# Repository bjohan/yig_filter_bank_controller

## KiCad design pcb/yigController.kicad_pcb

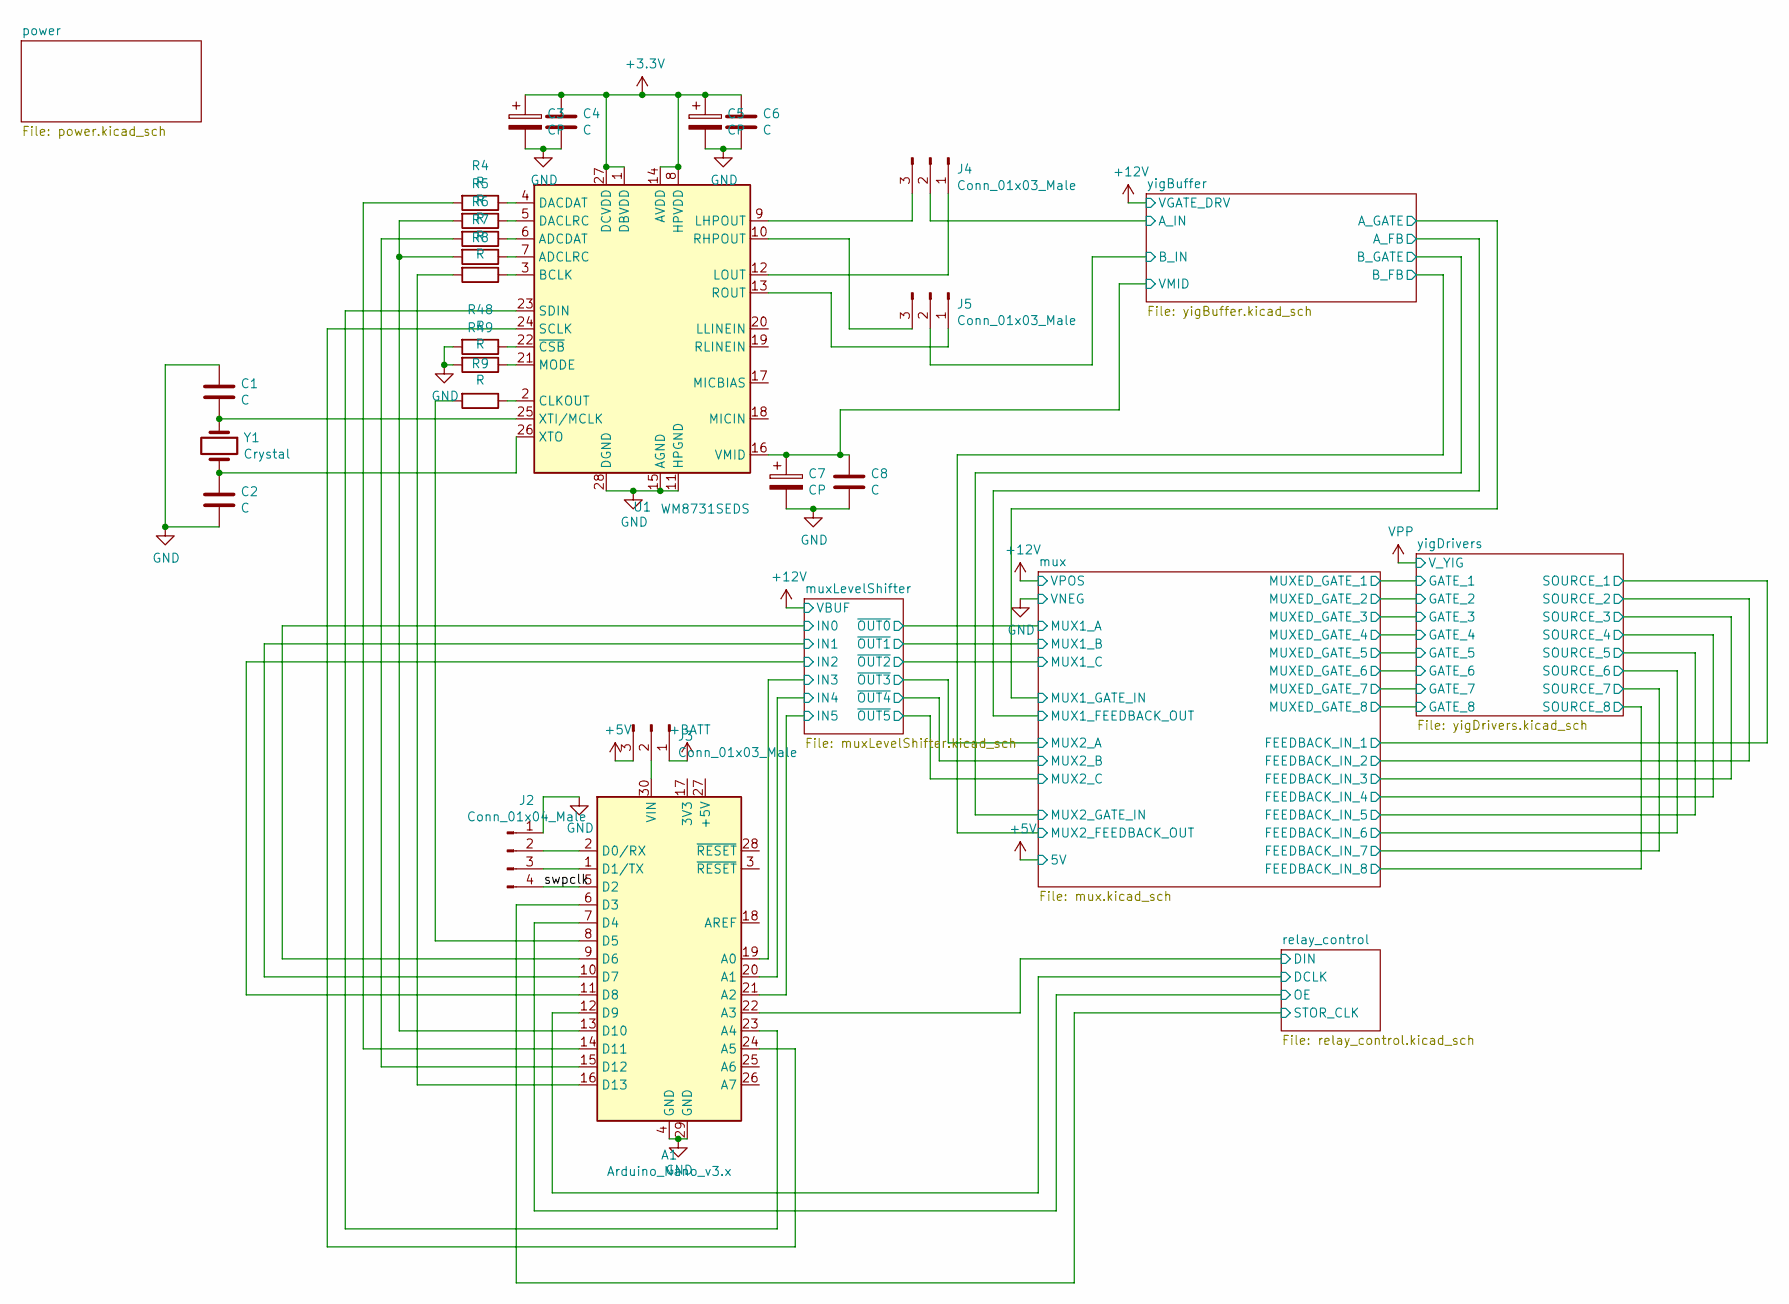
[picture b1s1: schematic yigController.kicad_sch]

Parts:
A1: Arduino_Nano_v3.x; Arduino_Nano
C1, C2, C4, C6, C8: C; C_1206_3216Metric
C3, C5, C7: CP; C_1206_3216Metric
J2: Conn_01x04_Male; PinHeader_1x04_P2.54mm_Vertical
J3, J4, J5: Conn_01x03_Male; PinHeader_1x03_P2.54mm_Vertical
R4, R5, R6, R7, R8, R9, R48, R49: R; R_1206_3216Metric
U1: WM8731SEDS; SSOP-28_5.3x10.2mm_P0.65mm
Y1: Crystal; Crystal_HC49-4H_Vertical

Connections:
+3V3: C3.1, C4.1, C5.1, C6.1, U1.1 (DBVDD), U1.8 (HPVDD), U1.14 (AVDD), U1.27 (DCVDD); also elsewhere on the board
+5V: J3.3; also elsewhere on the board
+BATT: J3.1; also elsewhere on the board
/muxLevelShifter/IN0: A1.9 (D6); also elsewhere on the board
/muxLevelShifter/IN1: A1.10 (D7); also elsewhere on the board
/muxLevelShifter/IN2: A1.11 (D8); also elsewhere on the board
/muxLevelShifter/IN3: A1.19 (A0); also elsewhere on the board
/muxLevelShifter/IN4: A1.20 (A1); also elsewhere on the board
/muxLevelShifter/IN5: A1.21 (A2); also elsewhere on the board
/relay_control/DCLK: A1.12 (D9); also elsewhere on the board
/relay_control/DIN: A1.22 (A3); also elsewhere on the board
/relay_control/OE: A1.7 (D4); also elsewhere on the board
/relay_control/STOR_CLK: A1.6 (D3); also elsewhere on the board
/swpclk: A1.5 (D2), J2.4
/yigBuffer/A_IN: J4.2; also elsewhere on the board
/yigBuffer/B_IN: J5.2; also elsewhere on the board
/yigBuffer/VMID: C7.1, C8.1, U1.16 (VMID); also elsewhere on the board
GND: A1.4 (GND), A1.29 (GND), C1.1, C2.2, C3.2, C4.2, C5.2, C6.2, C7.2, C8.2, J2.1, R48.2, R49.2, U1.11 (HPGND), U1.15 (AGND), U1.28 (DGND); also elsewhere on the board
unnamed: A1.1 (D1/TX), J2.3
unnamed: A1.2 (D0/RX), J2.2
unnamed: A1.8 (D5), R9.2
unnamed: A1.13 (D10), R5.2, R7.2
unnamed: A1.14 (D11), R4.2
unnamed: A1.15 (D12), R6.2
unnamed: A1.16 (D13), R8.2
unnamed: A1.23 (A4), U1.23 (SDIN)
unnamed: A1.24 (A5), U1.24 (SCLK)
unnamed: A1.30 (VIN), J3.2
unnamed: C1.2, U1.25 (XTI/MCLK), Y1.1
unnamed: C2.1, U1.26 (XTO), Y1.2
unnamed: J4.1, U1.12 (LOUT)
unnamed: J4.3, U1.9 (LHPOUT)
unnamed: J5.1, U1.13 (ROUT)
unnamed: J5.3, U1.10 (RHPOUT)
unnamed: R4.1, U1.4 (DACDAT)
unnamed: R5.1, U1.5 (DACLRC)
unnamed: R6.1, U1.6 (ADCDAT)
unnamed: R7.1, U1.7 (ADCLRC)
unnamed: R8.1, U1.3 (BCLK)
unnamed: R9.1, U1.2 (CLKOUT)
unnamed: R48.1, U1.22 (~CSB)
unnamed: R49.1, U1.21 (MODE)

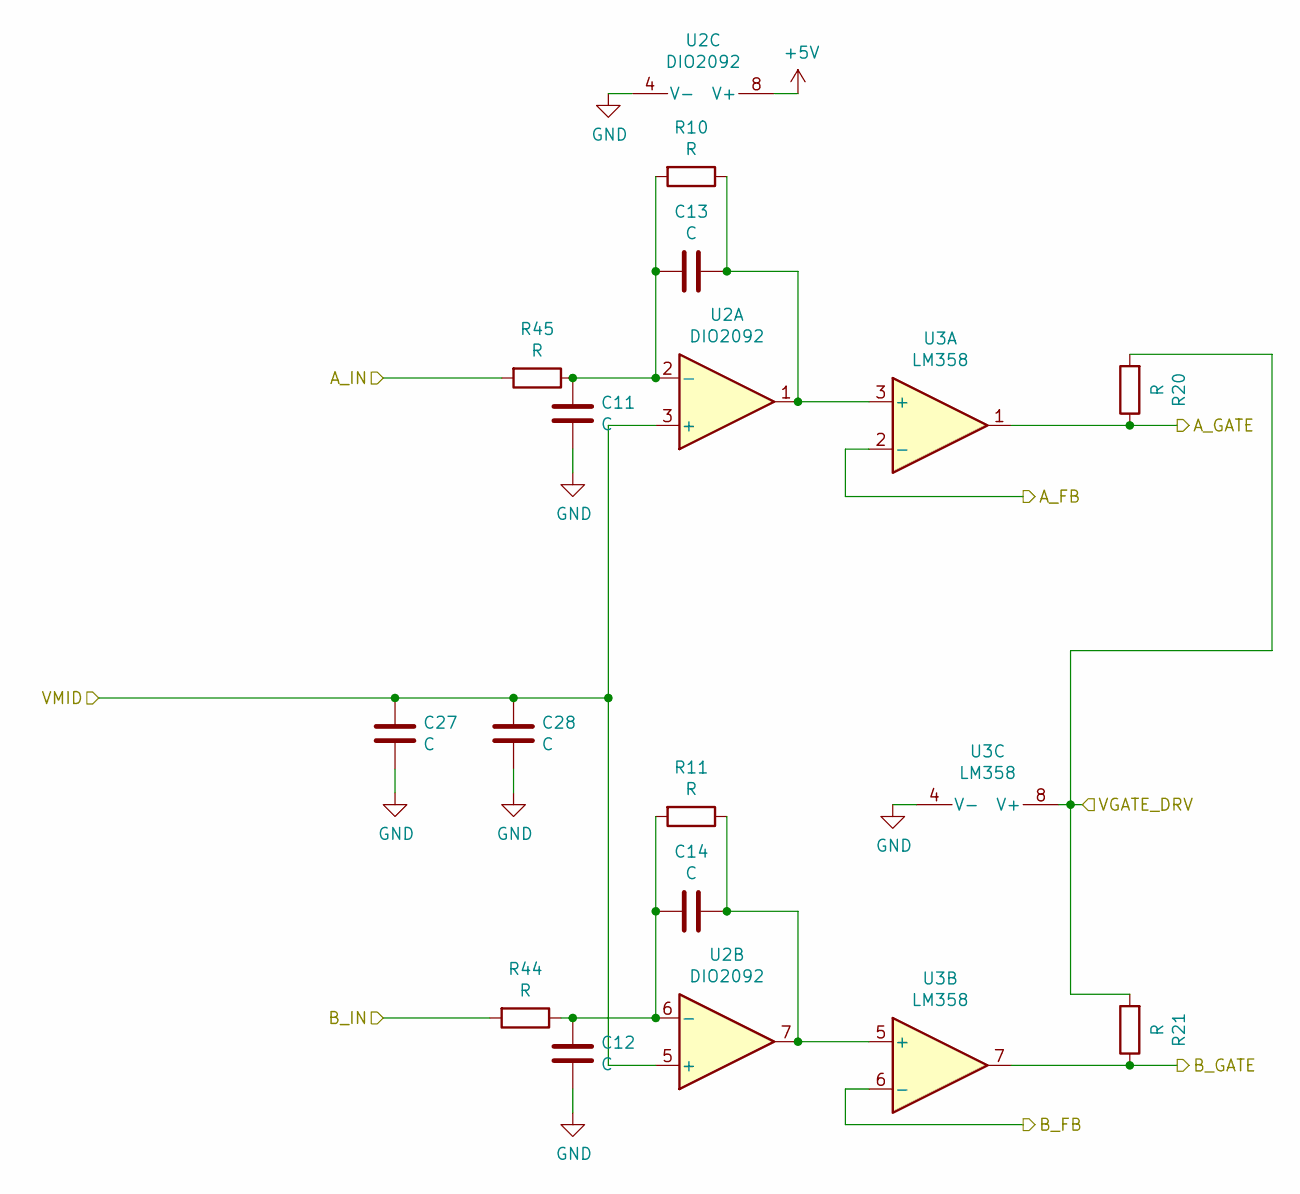
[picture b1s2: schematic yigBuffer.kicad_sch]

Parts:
C11, C12, C13, C14, C27, C28: C; C_1206_3216Metric
R10, R11, R20, R21, R44, R45: R; R_1206_3216Metric
U2: DIO2092; SOIC-8_3.9x4.9mm_P1.27mm
U3: LM358; SOIC-8_3.9x4.9mm_P1.27mm

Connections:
+5V: U2.8 (V+); also elsewhere on the board
+12V: R20.2, R21.2, U3.8 (V+); also elsewhere on the board
/yigBuffer/A_FB: U3.2 (-); also elsewhere on the board
/yigBuffer/A_GATE: R20.1, U3.1; also elsewhere on the board
/yigBuffer/A_IN: R45.2; also elsewhere on the board
/yigBuffer/B_FB: U3.6 (-); also elsewhere on the board
/yigBuffer/B_GATE: R21.1, U3.7; also elsewhere on the board
/yigBuffer/B_IN: R44.2; also elsewhere on the board
/yigBuffer/VMID: C27.1, C28.1, U2.3 (+), U2.5 (+); also elsewhere on the board
GND: C11.2, C12.2, C27.2, C28.2, U2.4 (V-), U3.4 (V-); also elsewhere on the board
unnamed: C11.1, C13.2, R10.2, R45.1, U2.2 (-)
unnamed: C12.1, C14.2, R11.2, R44.1, U2.6 (-)
unnamed: C13.1, R10.1, U2.1, U3.3 (+)
unnamed: C14.1, R11.1, U2.7, U3.5 (+)

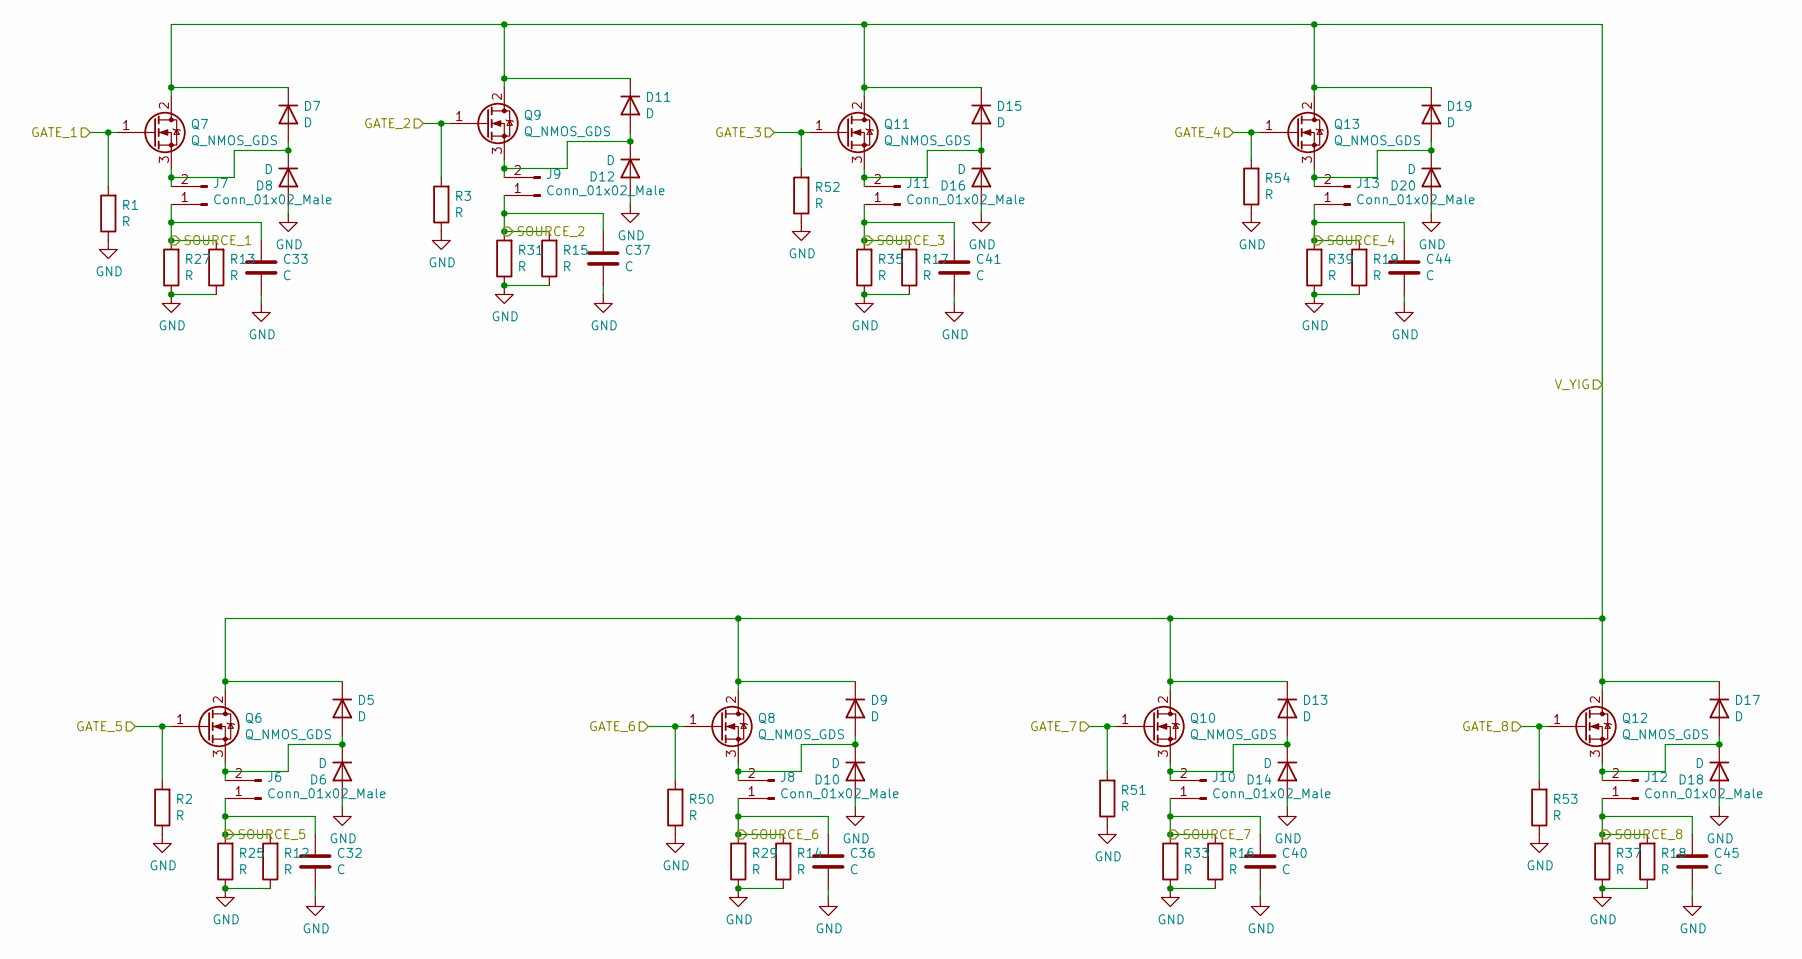
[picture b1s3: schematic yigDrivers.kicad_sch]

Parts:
C32, C33, C36, C37, C40, C41, C44, C45: C; C_1206_3216Metric
D5, D6, D7, D8, D9, D10, D11, D12, D13, D14, D15, D16, D17, D18, D19, D20: D; D_2010_5025Metric
J6, J7, J8, J9, J10, J11, J12, J13: Conn_01x02_Male; PinHeader_1x02_P2.54mm_Vertical
Q6, Q7, Q8, Q9, Q10, Q11, Q12, Q13: Q_NMOS_GDS; TO-220-3_Vertical
R1, R2, R3, R50, R51, R52, R53, R54: R; R_1206_3216Metric
R12, R13, R14, R15, R16, R17, R18, R19: R; R_2512_6332Metric
R25, R27, R29, R31, R33, R35, R37, R39: R; R_4020_10251Metric

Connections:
/mux/FEEDBACK_IN_1: C33.1, J7.1, R13.2, R27.2; also elsewhere on the board
/mux/FEEDBACK_IN_2: C37.1, J9.1, R15.2, R31.2; also elsewhere on the board
/mux/FEEDBACK_IN_3: C41.1, J11.1, R17.2, R35.2; also elsewhere on the board
/mux/FEEDBACK_IN_4: C44.1, J13.1, R19.2, R39.2; also elsewhere on the board
/mux/FEEDBACK_IN_5: C32.1, J6.1, R12.2, R25.2; also elsewhere on the board
/mux/FEEDBACK_IN_6: C36.1, J8.1, R14.2, R29.2; also elsewhere on the board
/mux/FEEDBACK_IN_7: C40.1, J10.1, R16.2, R33.2; also elsewhere on the board
/mux/FEEDBACK_IN_8: C45.1, J12.1, R18.2, R37.2; also elsewhere on the board
/yigDrivers/GATE_1: Q7.1 (G), R1.2; also elsewhere on the board
/yigDrivers/GATE_2: Q9.1 (G), R3.2; also elsewhere on the board
/yigDrivers/GATE_3: Q11.1 (G), R52.2; also elsewhere on the board
/yigDrivers/GATE_4: Q13.1 (G), R54.2; also elsewhere on the board
/yigDrivers/GATE_5: Q6.1 (G), R2.2; also elsewhere on the board
/yigDrivers/GATE_6: Q8.1 (G), R50.2; also elsewhere on the board
/yigDrivers/GATE_7: Q10.1 (G), R51.2; also elsewhere on the board
/yigDrivers/GATE_8: Q12.1 (G), R53.2; also elsewhere on the board
GND: C32.2, C33.2, C36.2, C37.2, C40.2, C41.2, C44.2, C45.2, D6.2 (A), D8.2 (A), D10.2 (A), D12.2 (A), D14.2 (A), D16.2 (A), D18.2 (A), D20.2 (A), R1.1, R2.1, R3.1, R12.1, R13.1, R14.1, R15.1, R16.1, R17.1, R18.1, R19.1, R25.1, R27.1, R29.1, R31.1, R33.1, R35.1, R37.1, R39.1, R50.1, R51.1, R52.1, R53.1, R54.1; also elsewhere on the board
unnamed: D5.2 (A), D6.1 (K), J6.2, Q6.3 (S)
unnamed: D7.2 (A), D8.1 (K), J7.2, Q7.3 (S)
unnamed: D9.2 (A), D10.1 (K), J8.2, Q8.3 (S)
unnamed: D11.2 (A), D12.1 (K), J9.2, Q9.3 (S)
unnamed: D13.2 (A), D14.1 (K), J10.2, Q10.3 (S)
unnamed: D15.2 (A), D16.1 (K), J11.2, Q11.3 (S)
unnamed: D17.2 (A), D18.1 (K), J12.2, Q12.3 (S)
unnamed: D19.2 (A), D20.1 (K), J13.2, Q13.3 (S)
VPP: D5.1 (K), D7.1 (K), D9.1 (K), D11.1 (K), D13.1 (K), D15.1 (K), D17.1 (K), D19.1 (K), Q6.2 (D), Q7.2 (D), Q8.2 (D), Q9.2 (D), Q10.2 (D), Q11.2 (D), Q12.2 (D), Q13.2 (D); also elsewhere on the board

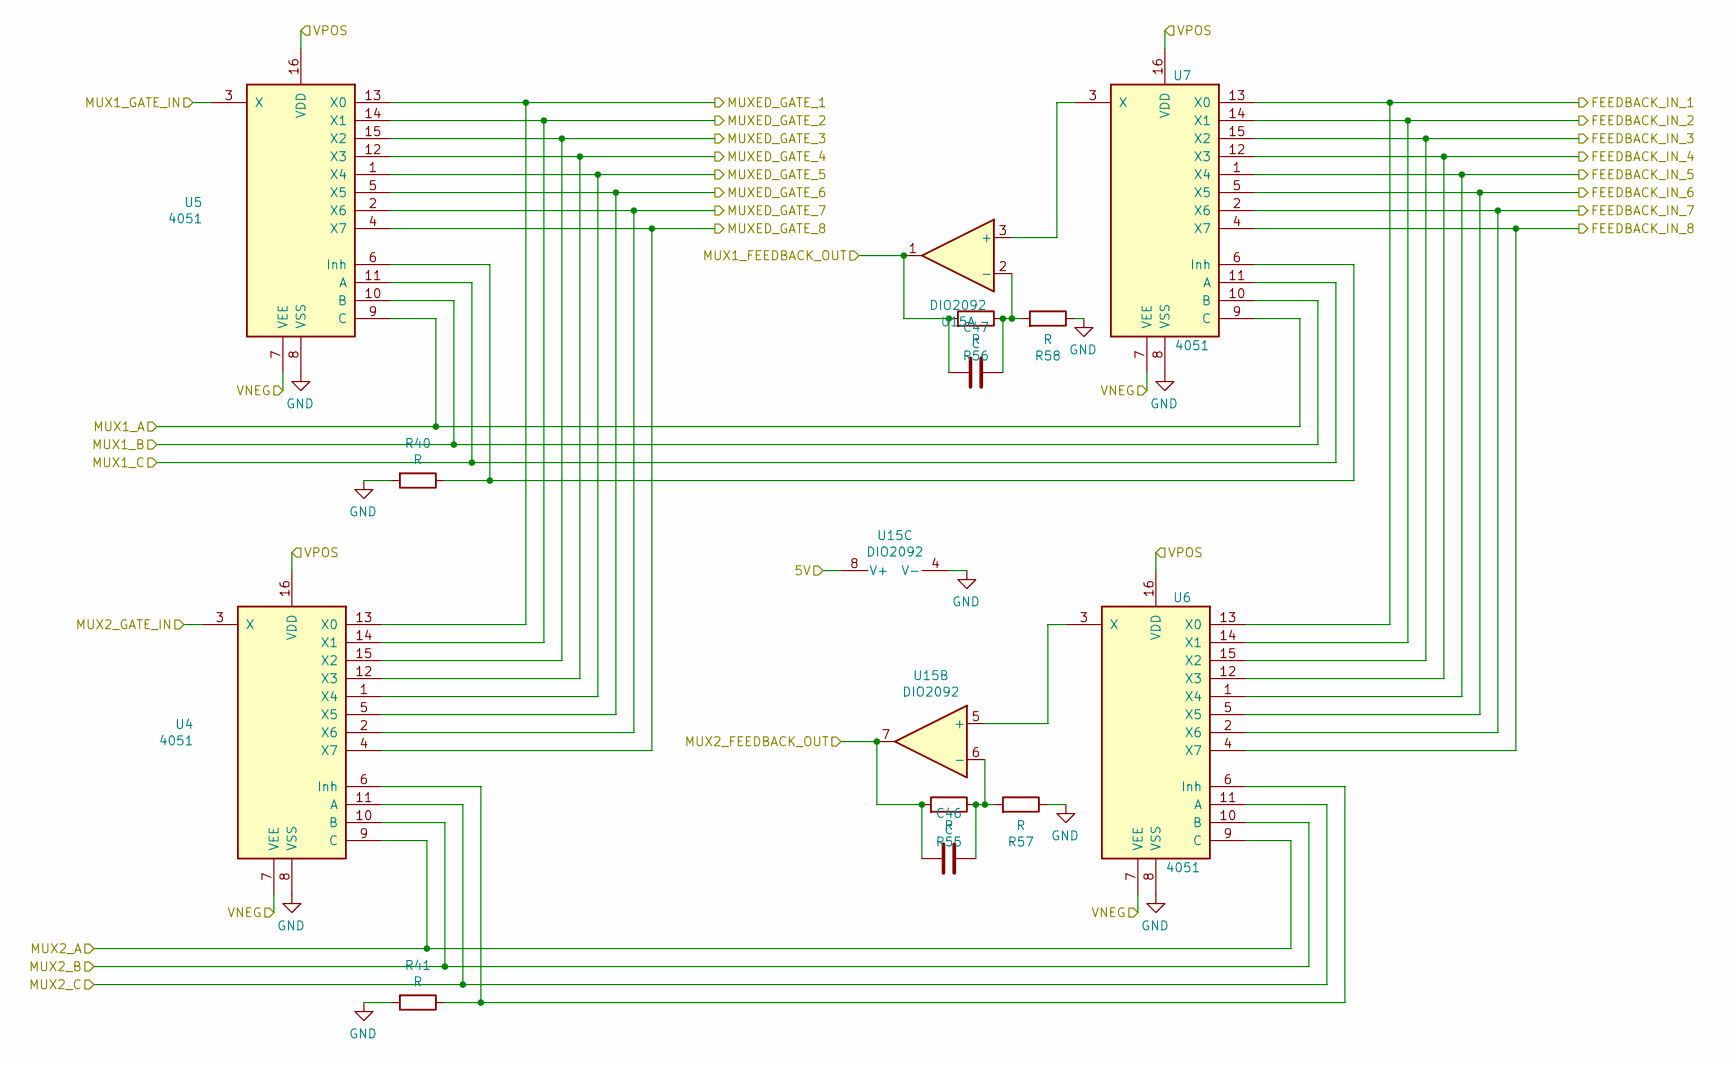
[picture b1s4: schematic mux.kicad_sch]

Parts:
C46, C47: C; C_1206_3216Metric
R40, R41, R55, R56, R57, R58: R; R_1206_3216Metric
U4, U5, U6, U7: 4051; SOIC-16_3.9x9.9mm_P1.27mm
U15: DIO2092; SOIC-8_3.9x4.9mm_P1.27mm

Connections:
+5V: U15.8 (V+); also elsewhere on the board
+12V: U4.16 (VDD), U5.16 (VDD), U6.16 (VDD), U7.16 (VDD); also elsewhere on the board
/mux/FEEDBACK_IN_1: U6.13 (X0), U7.13 (X0); also elsewhere on the board
/mux/FEEDBACK_IN_2: U6.14 (X1), U7.14 (X1); also elsewhere on the board
/mux/FEEDBACK_IN_3: U6.15 (X2), U7.15 (X2); also elsewhere on the board
/mux/FEEDBACK_IN_4: U6.12 (X3), U7.12 (X3); also elsewhere on the board
/mux/FEEDBACK_IN_5: U6.1 (X4), U7.1 (X4); also elsewhere on the board
/mux/FEEDBACK_IN_6: U6.5 (X5), U7.5 (X5); also elsewhere on the board
/mux/FEEDBACK_IN_7: U6.2 (X6), U7.2 (X6); also elsewhere on the board
/mux/FEEDBACK_IN_8: U6.4 (X7), U7.4 (X7); also elsewhere on the board
/mux/MUX1_A: U5.9 (C), U7.9 (C); also elsewhere on the board
/mux/MUX1_B: U5.10 (B), U7.10 (B); also elsewhere on the board
/mux/MUX1_C: U5.11 (A), U7.11 (A); also elsewhere on the board
/mux/MUX2_A: U4.9 (C), U6.9 (C); also elsewhere on the board
/mux/MUX2_B: U4.10 (B), U6.10 (B); also elsewhere on the board
/mux/MUX2_C: U4.11 (A), U6.11 (A); also elsewhere on the board
/yigBuffer/A_FB: C47.2, R56.2, U15.1; also elsewhere on the board
/yigBuffer/A_GATE: U5.3 (X); also elsewhere on the board
/yigBuffer/B_FB: C46.2, R55.2, U15.7; also elsewhere on the board
/yigBuffer/B_GATE: U4.3 (X); also elsewhere on the board
/yigDrivers/GATE_1: U4.13 (X0), U5.13 (X0); also elsewhere on the board
/yigDrivers/GATE_2: U4.14 (X1), U5.14 (X1); also elsewhere on the board
/yigDrivers/GATE_3: U4.15 (X2), U5.15 (X2); also elsewhere on the board
/yigDrivers/GATE_4: U4.12 (X3), U5.12 (X3); also elsewhere on the board
/yigDrivers/GATE_5: U4.1 (X4), U5.1 (X4); also elsewhere on the board
/yigDrivers/GATE_6: U4.5 (X5), U5.5 (X5); also elsewhere on the board
/yigDrivers/GATE_7: U4.2 (X6), U5.2 (X6); also elsewhere on the board
/yigDrivers/GATE_8: U4.4 (X7), U5.4 (X7); also elsewhere on the board
GND: R40.2, R41.2, R57.1, R58.1, U4.7 (VEE), U4.8 (VSS), U5.7 (VEE), U5.8 (VSS), U6.7 (VEE), U6.8 (VSS), U7.7 (VEE), U7.8 (VSS), U15.4 (V-); also elsewhere on the board
unnamed: C46.1, R55.1, R57.2, U15.6 (-)
unnamed: C47.1, R56.1, R58.2, U15.2 (-)
unnamed: R40.1, U5.6 (Inh), U7.6 (Inh)
unnamed: R41.1, U4.6 (Inh), U6.6 (Inh)
unnamed: U7.3 (X), U15.3 (+)
unnamed: U6.3 (X), U15.5 (+)

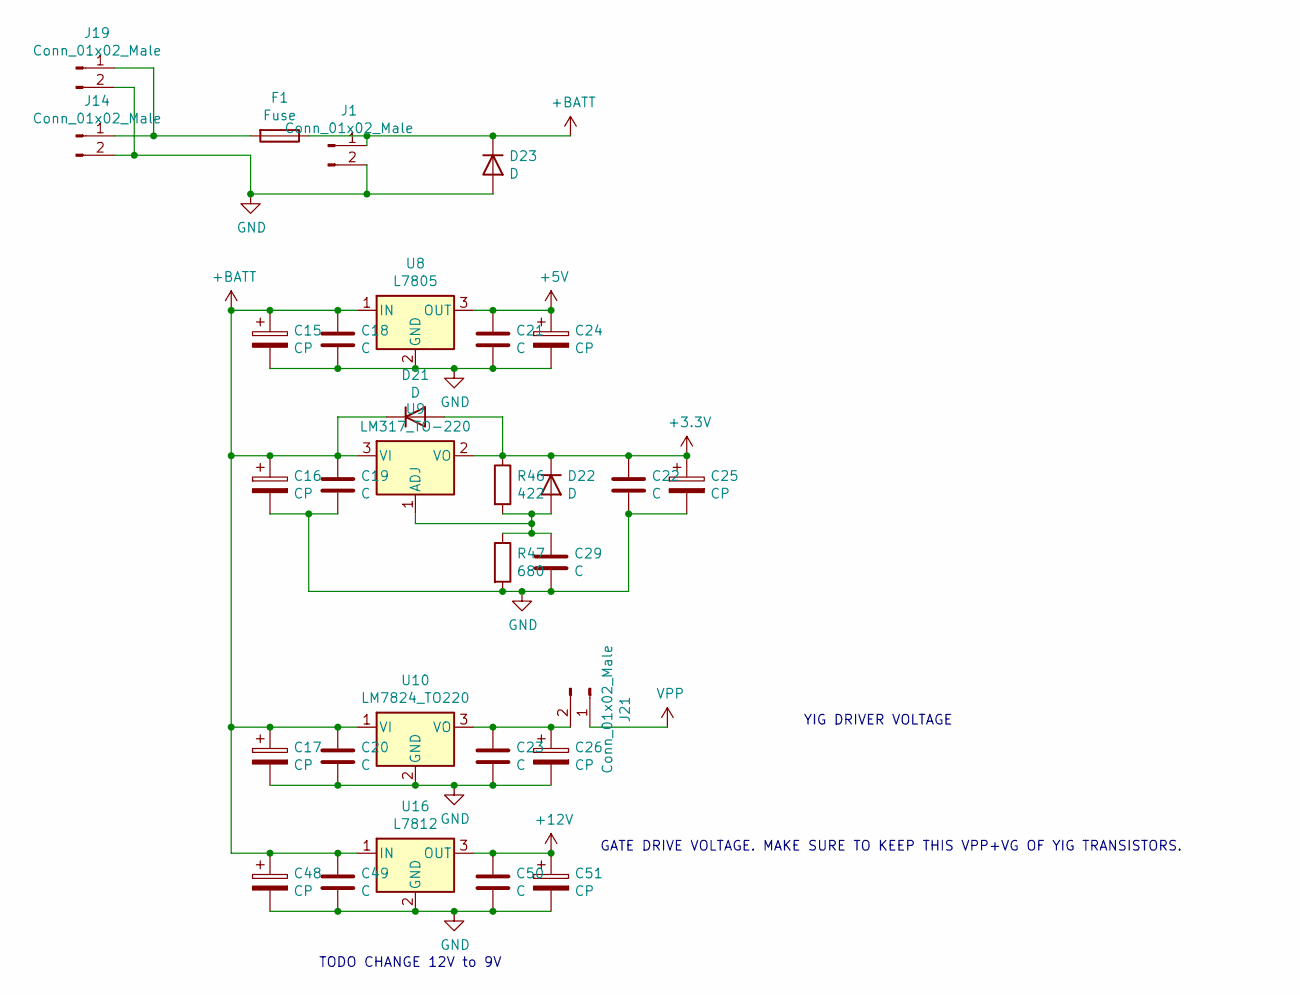
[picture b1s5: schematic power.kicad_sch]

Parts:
C15, C16, C17, C24, C25, C26, C48, C51: CP; CP_Elec_10x12.5
C18, C19, C20, C21, C22, C23, C29, C49, C50: C; C_1206_3216Metric
D21, D22, D23: D; D_2010_5025Metric
F1: Fuse; Fuse_1206_3216Metric
J1, J14, J19, J21: Conn_01x02_Male; PinHeader_1x02_P2.54mm_Vertical
R46: 422; R_1206_3216Metric
R47: 680; R_1206_3216Metric
U8: L7805; TO-220-3_Vertical
U9: LM317_TO-220; TO-220-3_Vertical
U10: LM7824_TO220; TO-220-3_Vertical
U16: L7812; TO-220-3_Vertical

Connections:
+3V3: C22.1, C25.1, D21.2 (A), D22.1 (K), R46.1, U9.2 (VO); also elsewhere on the board
+5V: C21.1, C24.1, U8.3 (OUT); also elsewhere on the board
+12V: C50.1, C51.1, U16.3 (OUT); also elsewhere on the board
+BATT: C15.1, C16.1, C17.1, C18.1, C19.1, C20.1, C48.1, C49.1, D21.1 (K), D23.1 (K), F1.1, J1.1, U8.1 (IN), U9.3 (VI), U10.1 (VI), U16.1 (IN); also elsewhere on the board
GND: C15.2, C16.2, C17.2, C18.2, C19.2, C20.2, C21.2, C22.2, C23.2, C24.2, C25.2, C26.2, C29.2, C48.2, C49.2, C50.2, C51.2, D23.2 (A), J1.2, J14.2, J19.2, R47.2, U8.2 (GND), U10.2 (GND), U16.2 (GND); also elsewhere on the board
unnamed: C23.1, C26.1, J21.2, U10.3 (VO)
unnamed: C29.1, D22.2 (A), R46.2, R47.1, U9.1 (ADJ)
unnamed: F1.2, J14.1, J19.1
VPP: J21.1; also elsewhere on the board

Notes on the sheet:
YIG DRIVER VOLTAGE
TODO CHANGE 12V to 9V
GATE DRIVE VOLTAGE. MAKE SURE TO KEEP THIS VPP+VG OF YIG TRANSISTORS.

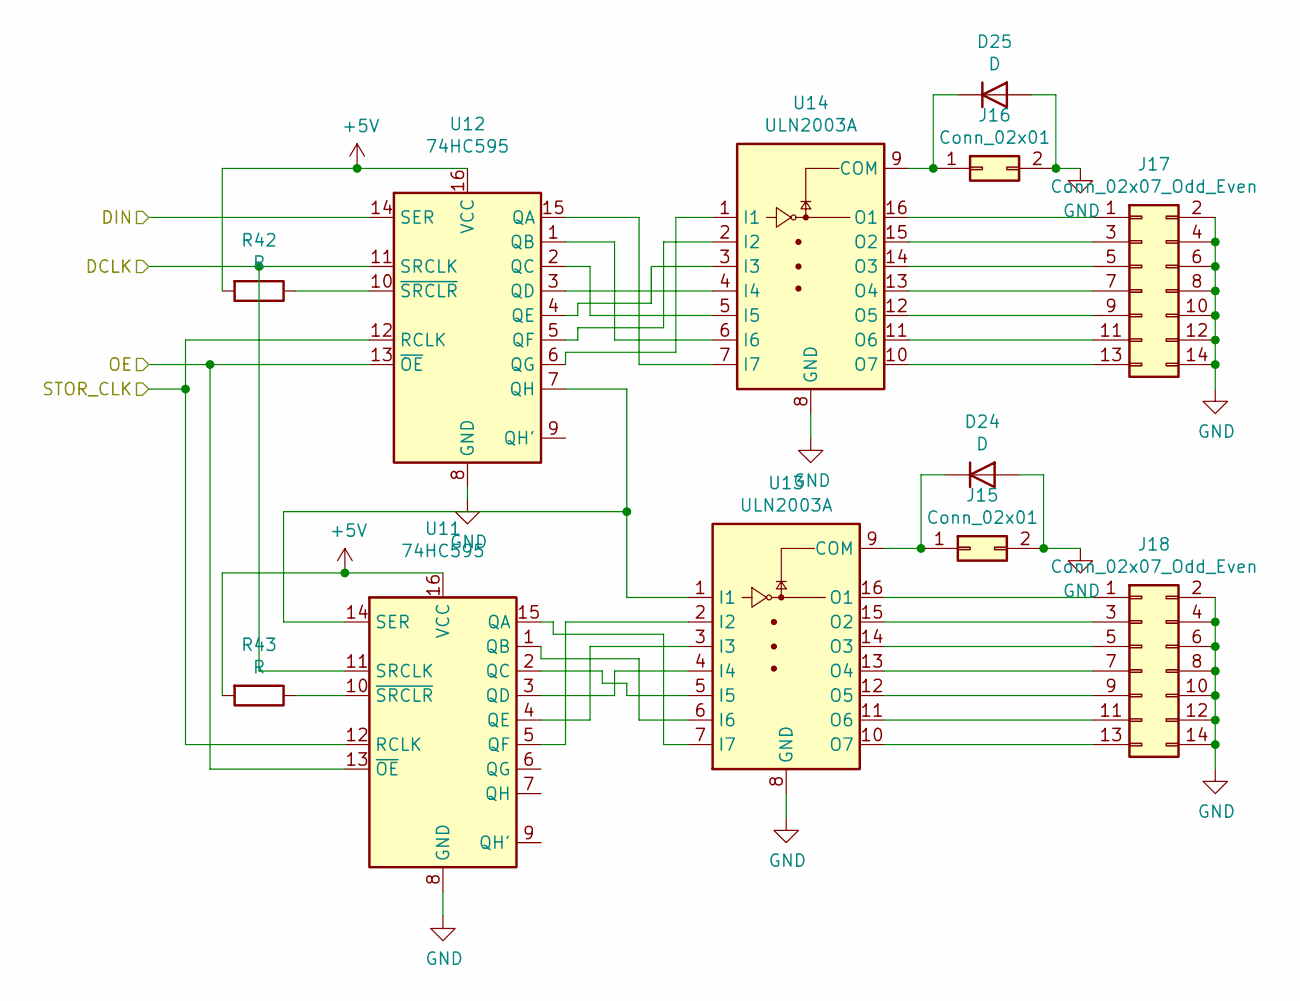
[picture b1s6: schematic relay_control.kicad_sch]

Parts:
D24, D25: D; D_2010_5025Metric
J15, J16: Conn_02x01; PinHeader_1x02_P2.54mm_Vertical
J17, J18: Conn_02x07_Odd_Even; PinHeader_2x07_P2.54mm_Vertical
R42, R43: R; R_1206_3216Metric
U11, U12: 74HC595; TSSOP-16_4.4x5mm_P0.65mm
U13, U14: ULN2003A; SOIC-16_3.9x9.9mm_P1.27mm

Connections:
+5V: R42.2, R43.2, U11.16 (VCC), U12.16 (VCC); also elsewhere on the board
/relay_control/DCLK: U11.11 (SRCLK), U12.11 (SRCLK); also elsewhere on the board
/relay_control/DIN: U12.14 (SER); also elsewhere on the board
/relay_control/OE: U11.13 (~OE), U12.13 (~OE); also elsewhere on the board
/relay_control/STOR_CLK: U11.12 (RCLK), U12.12 (RCLK); also elsewhere on the board
GND: D24.2 (A), D25.2 (A), J15.2, J16.2, J17.2, J17.4, J17.6, J17.8, J17.10, J17.12, J17.14, J18.2, J18.4, J18.6, J18.8, J18.10, J18.12, J18.14, U11.8 (GND), U12.8 (GND), U13.8 (GND), U14.8 (GND); also elsewhere on the board
unnamed: D24.1 (K), J15.1, U13.9 (COM)
unnamed: D25.1 (K), J16.1, U14.9 (COM)
unnamed: J17.1, U14.16 (O1)
unnamed: J17.3, U14.15 (O2)
unnamed: J17.5, U14.14 (O3)
unnamed: J17.7, U14.13 (O4)
unnamed: J17.9, U14.12 (O5)
unnamed: J17.11, U14.11 (O6)
unnamed: J17.13, U14.10 (O7)
unnamed: J18.1, U13.16 (O1)
unnamed: J18.3, U13.15 (O2)
unnamed: J18.5, U13.14 (O3)
unnamed: J18.7, U13.13 (O4)
unnamed: J18.9, U13.12 (O5)
unnamed: J18.11, U13.11 (O6)
unnamed: J18.13, U13.10 (O7)
unnamed: R42.1, U12.10 (~SRCLR)
unnamed: R43.1, U11.10 (~SRCLR)
unnamed: U11.1 (QB), U13.6 (I6)
unnamed: U11.2 (QC), U13.5 (I5)
unnamed: U11.3 (QD), U13.4 (I4)
unnamed: U11.4 (QE), U13.3 (I3)
unnamed: U11.5 (QF), U13.2 (I2)
unnamed: U11.14 (SER), U12.7 (QH), U13.1 (I1)
unnamed: U11.15 (QA), U13.7 (I7)
unnamed: U12.1 (QB), U14.6 (I6)
unnamed: U12.2 (QC), U14.5 (I5)
unnamed: U12.3 (QD), U14.4 (I4)
unnamed: U12.4 (QE), U14.3 (I3)
unnamed: U12.5 (QF), U14.2 (I2)
unnamed: U12.6 (QG), U14.1 (I1)
unnamed: U12.15 (QA), U14.7 (I7)

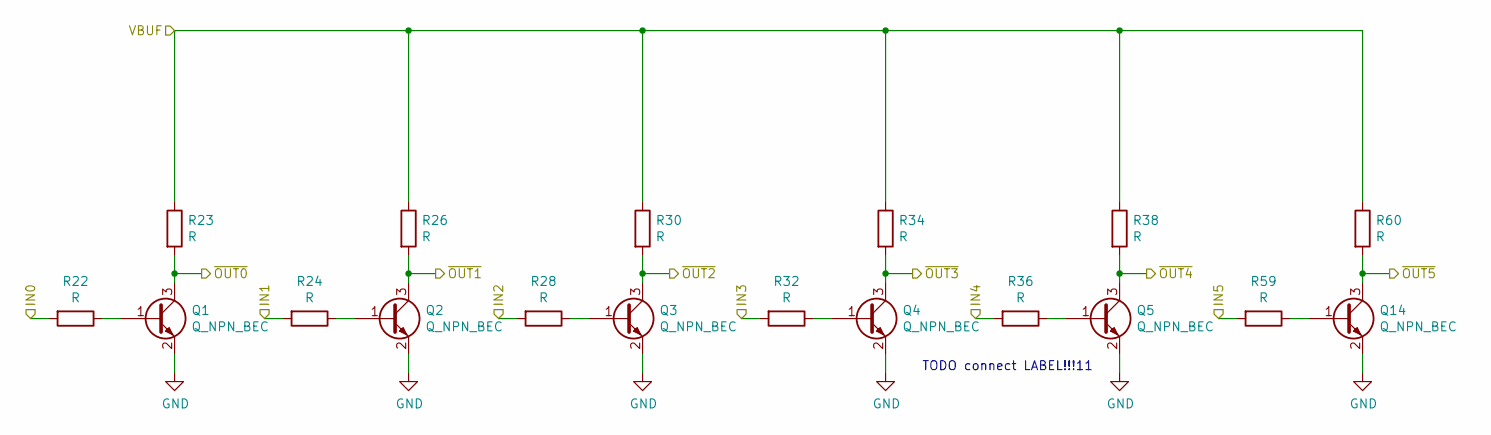
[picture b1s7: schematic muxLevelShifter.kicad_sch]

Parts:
Q1, Q2, Q3, Q4, Q5, Q14: Q_NPN_BEC; SOT-23
R22, R23, R24, R26, R28, R30, R32, R34, R36, R38, R59, R60: R; R_1206_3216Metric

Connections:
+12V: R23.1, R26.1, R30.1, R34.1, R38.1, R60.1; also elsewhere on the board
/mux/MUX1_A: Q1.3 (C), R23.2; also elsewhere on the board
/mux/MUX1_B: Q2.3 (C), R26.2; also elsewhere on the board
/mux/MUX1_C: Q3.3 (C), R30.2; also elsewhere on the board
/mux/MUX2_A: Q4.3 (C), R34.2; also elsewhere on the board
/mux/MUX2_B: Q5.3 (C), R38.2; also elsewhere on the board
/mux/MUX2_C: Q14.3 (C), R60.2; also elsewhere on the board
/muxLevelShifter/IN0: R22.2; also elsewhere on the board
/muxLevelShifter/IN1: R24.2; also elsewhere on the board
/muxLevelShifter/IN2: R28.2; also elsewhere on the board
/muxLevelShifter/IN3: R32.2; also elsewhere on the board
/muxLevelShifter/IN4: R36.2; also elsewhere on the board
/muxLevelShifter/IN5: R59.2; also elsewhere on the board
GND: Q1.2 (E), Q2.2 (E), Q3.2 (E), Q4.2 (E), Q5.2 (E), Q14.2 (E); also elsewhere on the board
unnamed: Q1.1 (B), R22.1
unnamed: Q2.1 (B), R24.1
unnamed: Q3.1 (B), R28.1
unnamed: Q4.1 (B), R32.1
unnamed: Q5.1 (B), R36.1
unnamed: Q14.1 (B), R59.1

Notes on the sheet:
TODO connect LABEL!!!11

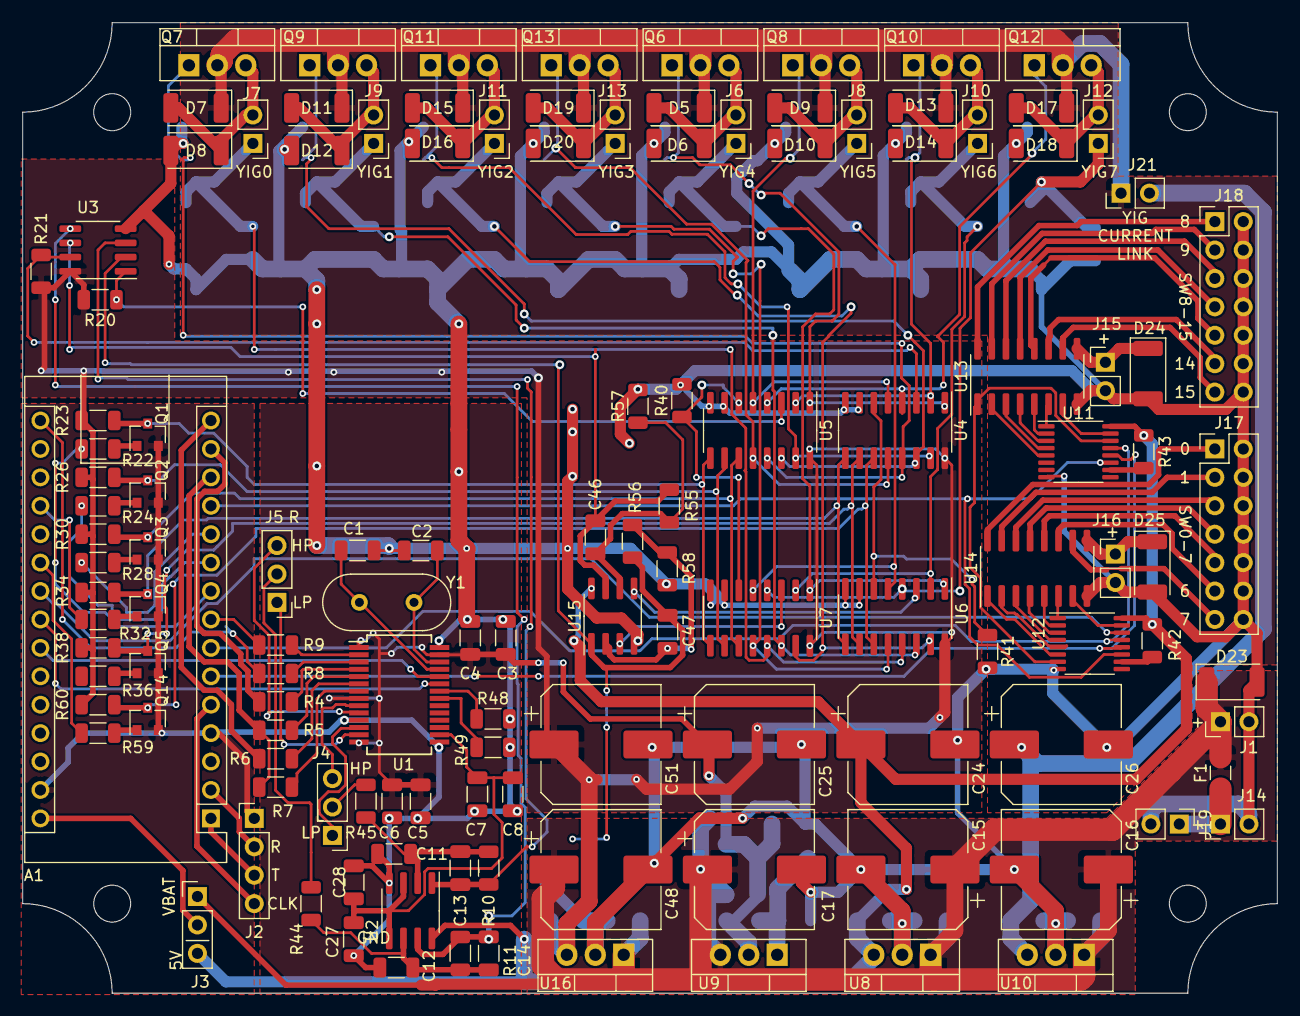
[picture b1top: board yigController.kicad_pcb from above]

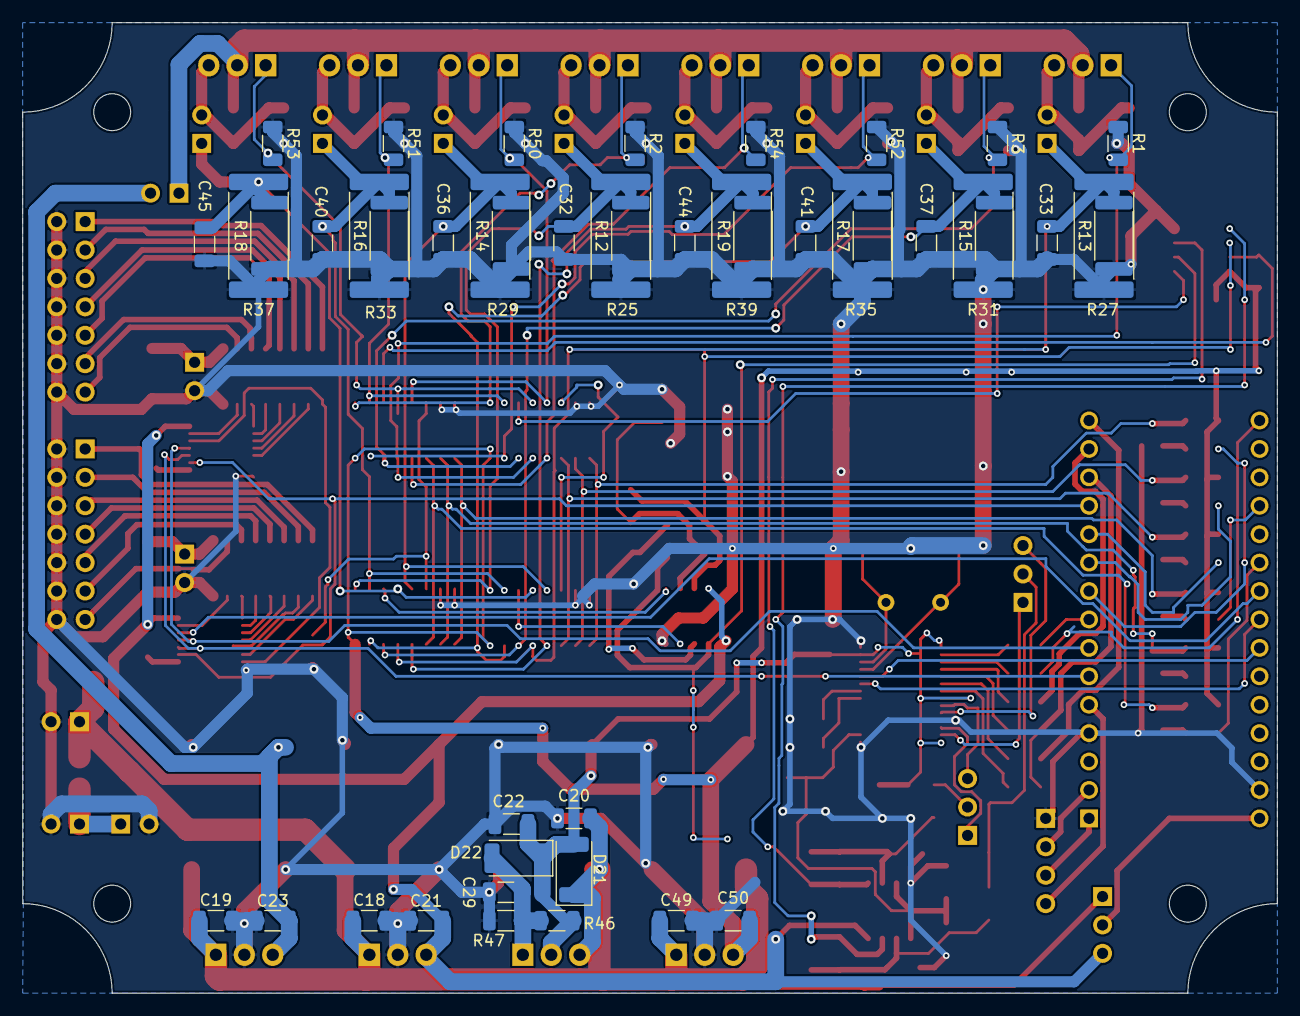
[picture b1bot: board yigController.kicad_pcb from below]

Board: 2 copper layers, 112.1 x 86.7 mm, 175 parts (45 on the bottom side), 129 nets.

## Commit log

2022-04-17 Added existing code, needs to be integrated
2022-04-18 started troubleshooting instability
2022-04-18 fixed submodule
2022-04-18 gitignore
2022-04-19 Continued troubleshooting
2022-05-01 More testing
2022-05-02 Added more measurements in notebook for automatic yig filter learning
2022-05-02 Started adding coarse frequency sweep
2022-05-03 Added drift measurements
2022-05-06 Added measurements to get data for filter fine tuning
2022-05-07 Added some variables for hw revision. Added measurementdata for 2.1, yig filter at source side of mosfet
2022-05-07 Measured revised hardware
2022-05-08 Added fine tuning
2022-05-10 measurement for both channels
2022-05-10 Added initial arduino sketch
2022-05-17 More measurements
2022-05-17 Measured using new tuning
2022-05-18 Better strings
2022-05-18 Fixed coefficients
2022-05-19 Tested filter bank sweep
2022-05-19 Sweept entire band in 10MHz increments
2022-06-09 Added some measurements for version 3 of the pcb
2022-12-11 Rearranged some files
2022-12-11 Small changes in code to be able to run on mega168
2022-12-11 Renamed arduino sketch and folder
2022-12-11 Added slightly cleand up yig controller library
2024-03-17 Updated to work with newer versions of arduino-mk and SerialCommands-library
2024-03-17 Added channel support to yig_controller.py
2024-11-19 Added pcb
2024-11-19 Added plot and updated to newer kicad version
